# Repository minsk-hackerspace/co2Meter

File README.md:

# C02 Meter
ESP8266 + MZ-H19b + DHT11 + Oled1.3 = CO2 Meter

# Result

# Scheme

# ShopList:

- https://www.aliexpress.com/item/-/32860834286.html

- https://www.aliexpress.com/item/-/32802874451.html (cp2102)

- https://www.aliexpress.com/item/-/32844104782.html (1.3 White 7-pin SPI)

# Components

# HomeAssistant
Using esphome, in `./esphomeFirmware`.

# Licensed under WTFPL

- http://www.wtfpl.net/

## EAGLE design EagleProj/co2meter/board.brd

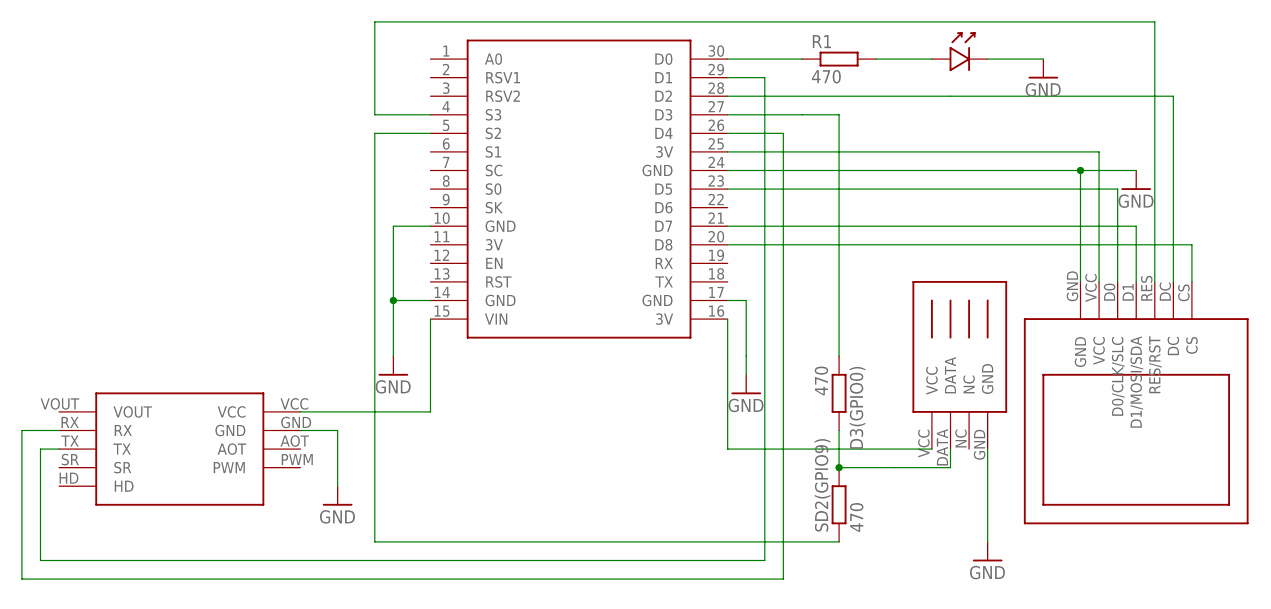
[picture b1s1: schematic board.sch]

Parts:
D3(GPIO0): 470; M1206
R1: 470; M1206
SD2(GPIO9): 470; M1206
U$1: NODEMCUV3; NODEMCU_V3
U$2: DHT11DEF; DHT11
U$3: MH_Z19BDEF; MH_Z19B
U$4: OLED_1.3_V2.0DEF; OLED_1.3_V2.0
U$6: LED_3MLED3M_3D; LEDRD254W60D300H500B

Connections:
3V: U$1.11 (3V)
GND: U$1.10 (GND), U$1.14 (GND), U$1.17 (GND), U$1.24 (GND), U$2.GND, U$3.GND, U$4.GND, U$6.2 (K)
unnamed: R1.1, U$1.30 (D0)
unnamed: D3(GPIO0).2, SD2(GPIO9).2, U$2.DATA
unnamed: U$1.4 (S3), U$4.RES (RES/RST)
unnamed: R1.2, U$6.1 (A)
unnamed: U$1.20 (D8), U$4.CS
unnamed: U$1.28 (D2), U$4.DC
unnamed: U$1.21 (D7), U$4.D1 (D1/MOSI/SDA)
unnamed: U$1.23 (D5), U$4.D0 (D0/CLK/SLC)
unnamed: U$1.15 (VIN), U$3.VCC
unnamed: U$1.26 (D4), U$3.RX
unnamed: U$1.29 (D1), U$3.TX
unnamed: U$1.16 (3V), U$2.VCC
unnamed: U$1.25 (3V), U$4.VCC
unnamed: SD2(GPIO9).1, U$1.5 (S2)
unnamed: D3(GPIO0).1, U$1.27 (D3)

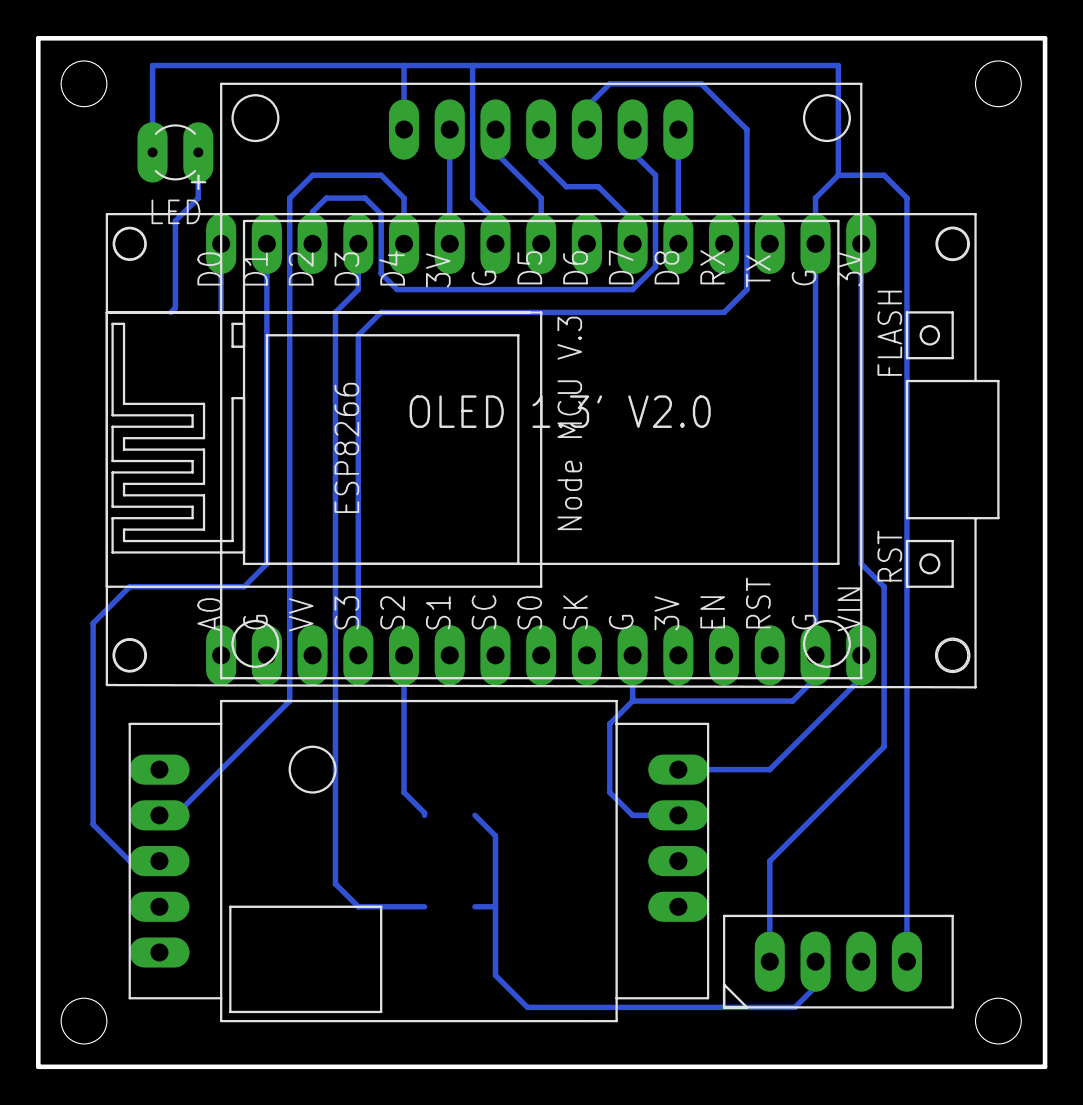
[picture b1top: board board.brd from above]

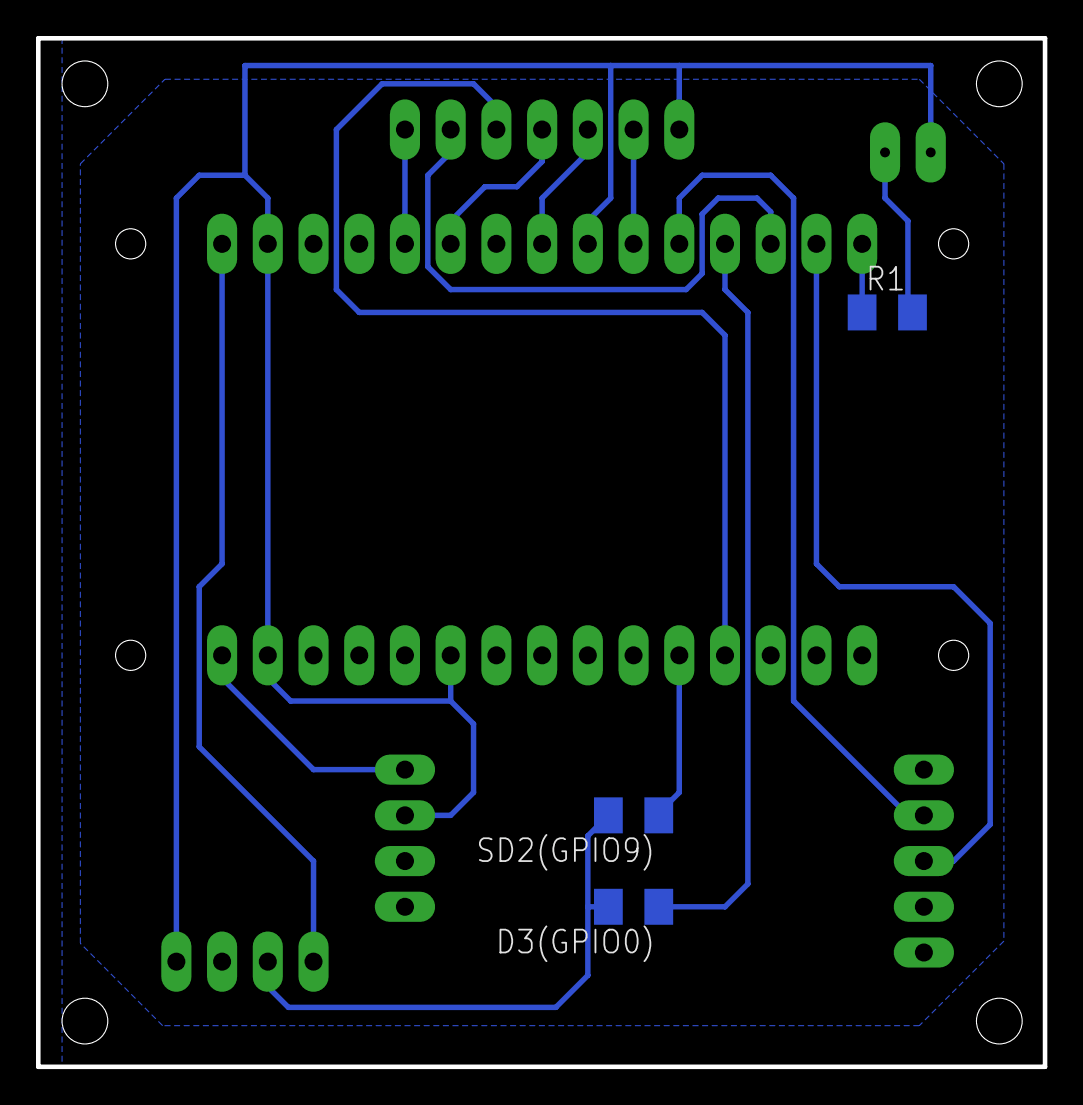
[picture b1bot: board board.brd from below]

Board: 2 copper layers, 55.9 x 57.1 mm, 8 parts (3 on the bottom side), 16 nets.

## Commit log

2018-05-09 Update some status led
2019-02-10 Co2 meter update with adafruit io
2019-02-10 Add saving settings
2019-04-07 Add DHT functions
2019-04-07 Add some images
2019-04-07 add image
2019-04-07 Coding style: remove redundant whitespaces
2019-04-07 Add compile-time setting for display type
2019-04-07 Coding style: change indents to 4-space
2019-04-07 Support an I2C interface for OLED display
2020-04-11 Add esphome and homeassistant support
2020-04-11 Add home assistant screenshot
